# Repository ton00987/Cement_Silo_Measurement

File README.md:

# Cement_Silo_Measurement
/*
* Demo   : Silo measurement 
* VERSION: 0.1 (2/8/2019)
*
* MCU    : ESP32(ESP-WROOM-32)
*
* Output : Wifi
*        : BLYNK
*        : ThingSpeak
*
* Demo   : BLYNK -> "SILO MEASUREMENT"
*        : Blynk library V0.6.1
*        : BME280 
*        : MPU6050
*        :  
* Widget : RESET_B_pin              V1
*        : Widget_HEIGHT_BME        V5
*        : Widget_HEIGHT_MPU        V6
*        : Widget_Terminal          V7
*        : Widget_LED_RED_Status    V14
*        : Widget_LED_GREEN_Status  V27
*        : Widget_LED_BLUE_Status   V26
*/

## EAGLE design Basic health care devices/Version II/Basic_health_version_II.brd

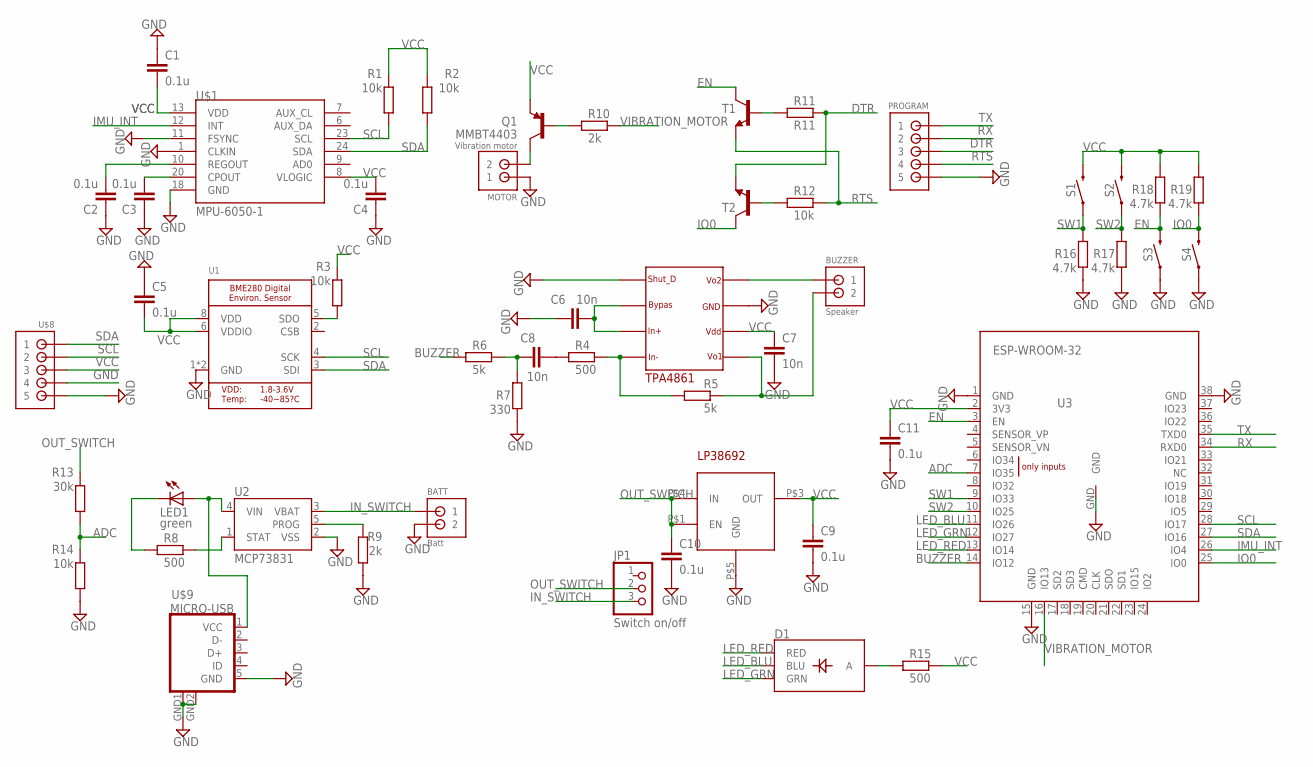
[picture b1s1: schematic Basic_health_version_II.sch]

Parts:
BATT: Batt; JST_B2B-PH_HEADER
BUZZER: Speaker; JST_B2B-PH_HEADER
C1, C2, C3, C4, C5, C9, C10, C11: 0.1u; C0603K
C6, C7, C8: 10n; C0603K
D1: LED-RGB-CASMD; LED-TRICOLOR-SMD
JP1: Switch on/off; 1X03
LED1: green; CHIPLED_0805
MOTOR: Vibration motor; JST_B2B-PH_HEADER
PROGRAM: Program port; JST_B5B-PH_HEADER
Q1: MMBT4403; SOT23-3
R1, R2, R3, R12, R14: 10k; R0603
R4, R8, R15: 500; R0603
R5, R6: 5k; R0603
R7: 330; R0603
R9, R10: 2k; R0603
R11: R11; R0603
R13: 30k; R0603
R16, R17, R18, R19: 4.7k; R0603
S1, S2, S3, S4: MOMENTARY-SWITCH-SPST-PTH-RIGHT-ANGLE; TACTILE_SWITCH_PTH_RIGHT_ANGLE
T1, T2: BC817-16-NPN-SOT23-BEC; SOT23-BEC
U1: BME280
U2: MCP73831; SOT23-5
U3: ESP-WROOM-32
U$1: MPU-6050-1; QFN-24-4MM2
U$2: TPA4861; SOIC8
U$5: LP38692_3.3V; SOT-223-4
U$8: JST-PH_5-PIN_HEADER; JST_B5B-PH_HEADER
U$9: MICRO-USB

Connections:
ADC: R13.1, R14.2, U3.7 (IO35)
BUZZER: R6.2, U3.14 (IO12)
DTR: PROGRAM.P3 (3), R11.1, T2.E
EN: R18.2, S3.2, T1.C, U3.3 (EN)
GND: BATT.P2 (2), C1.1, C2.1, C3.1, C4.1, C5.1, C6.2, C7.2, C9.2, C10.2, C11.2, MOTOR.P1 (1), PROGRAM.P5 (5), R7.2, R9.2, R14.1, R16.2, R17.2, S3.1, S4.1, U1.1 (GND), U1.7 (GND), U2.2 (VSS), U3.1 (GND), U3.15 (GND), U3.38 (GND), U3.GND, U$1.1 (CLKIN), U$1.11 (FSYNC), U$1.18 (GND), U$2.P$1, U$2.P$7, U$5.P$5 (GND), U$8.P4 (4), U$8.P5 (5), U$9.5 (GND), U$9.GND1 (GND), U$9.GND2 (GND)
IMU_INT: U3.26 (IO4), U$1.12 (INT)
IN_SWITCH: BATT.P1 (1), JP1.3, U2.3 (VBAT)
IO0: R19.2, S4.2, T2.C, U3.25 (IO0)
LED_BLU: D1.B (BLU), U3.11 (IO26)
LED_GRN: D1.G (GRN), U3.12 (IO27)
LED_RED: D1.R (RED), U3.13 (IO14)
unnamed: C6.1, U$2.P$2, U$2.P$3
unnamed: R3.1, U1.5 (SDO)
unnamed: C3.2, U$1.20 (CPOUT)
unnamed: C2.2, U$1.10 (REGOUT)
unnamed: R4.1, R5.2, U$2.P$4
unnamed: C8.2, R4.2
unnamed: BUZZER.P2 (2), R5.1, U$2.P$5
unnamed: BUZZER.P1 (1), U$2.P$8
unnamed: C8.1, R6.1, R7.1
unnamed: LED1.A, U2.4 (VIN), U$9.1 (VCC)
unnamed: LED1.C, R8.2
unnamed: R8.1, U2.1 (STAT)
unnamed: R9.1, U2.5 (PROG)
unnamed: Q1.1 (B), R10.2
unnamed: MOTOR.P2 (2), Q1.3 (C)
unnamed: R12.2, T2.B
unnamed: R11.2, T1.B
unnamed: D1.A, R15.2
OUT_SWITCH: C10.1, JP1.2, R13.2, U$5.P$1 (EN), U$5.P$4 (IN)
RTS: PROGRAM.P4 (4), R12.1, T1.E
RX: PROGRAM.P2 (2), U3.34 (RXD0)
SCL: R1.1, U1.4 (SCK), U3.28 (IO17), U$1.23 (SCL), U$8.P2 (2)
SDA: R2.1, U1.3 (SDI), U3.27 (IO16), U$1.24 (SDA), U$8.P1 (1)
SW1: R16.1, S1.1, U3.9 (IO33)
SW2: R17.1, S2.1, U3.10 (IO25)
TX: PROGRAM.P1 (1), U3.35 (TXD0)
VCC: C1.2, C4.2, C5.2, C7.1, C9.1, C11.1, Q1.2 (E), R1.2, R2.2, R3.2, R15.1, R18.1, R19.1, S1.2, S2.2, U1.6 (VDDIO), U1.8 (VDD), U3.2 (3V3), U$1.8 (VLOGIC), U$1.13 (VDD), U$2.P$6, U$5.P$3 (OUT), U$8.P3 (3)
VIBRATION_MOTOR: R10.1, U3.16 (IO13)

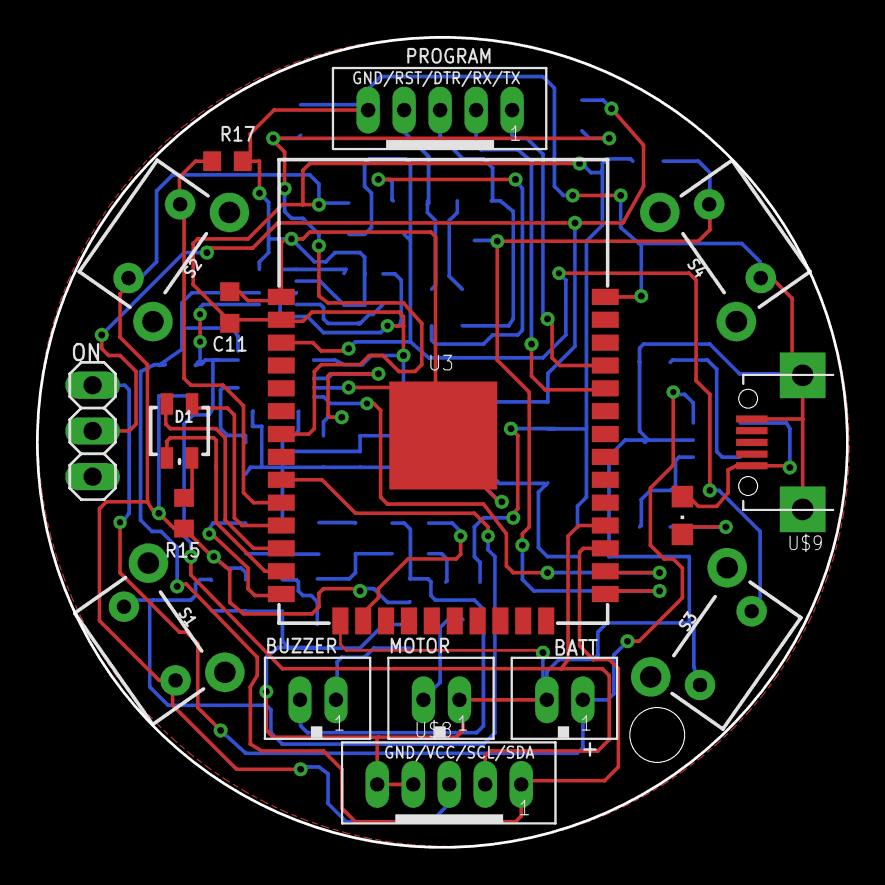
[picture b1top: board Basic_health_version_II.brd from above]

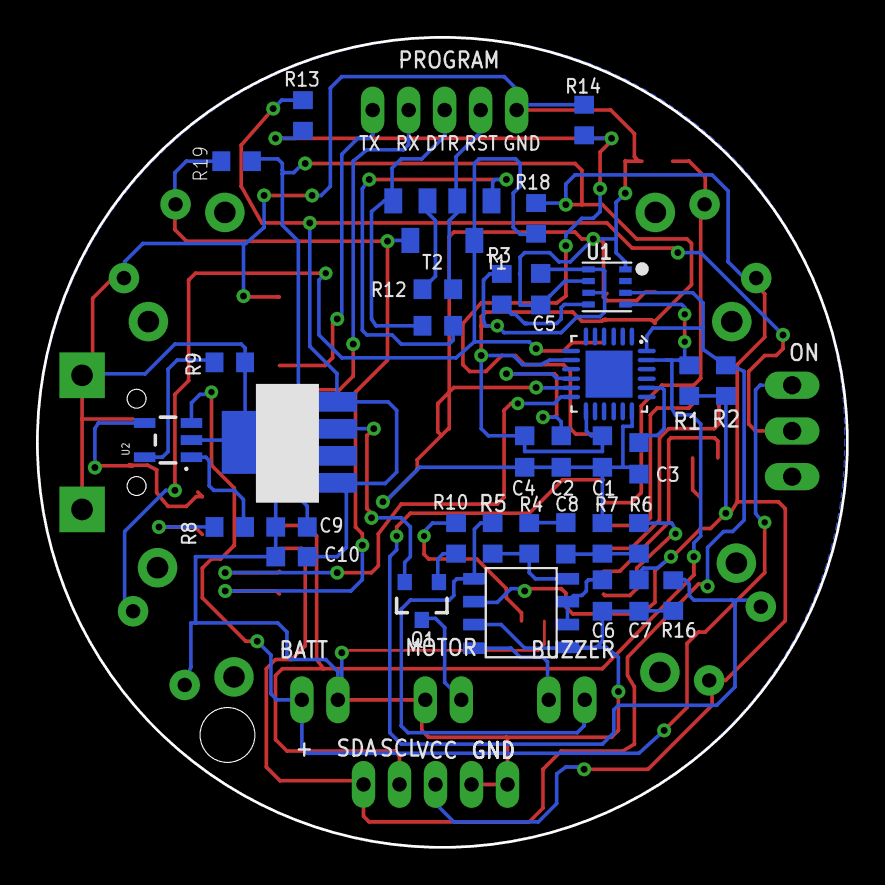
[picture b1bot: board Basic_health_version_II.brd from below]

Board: 2 copper layers, 45.0 x 45.0 mm, 52 parts (35 on the bottom side), 39 nets.

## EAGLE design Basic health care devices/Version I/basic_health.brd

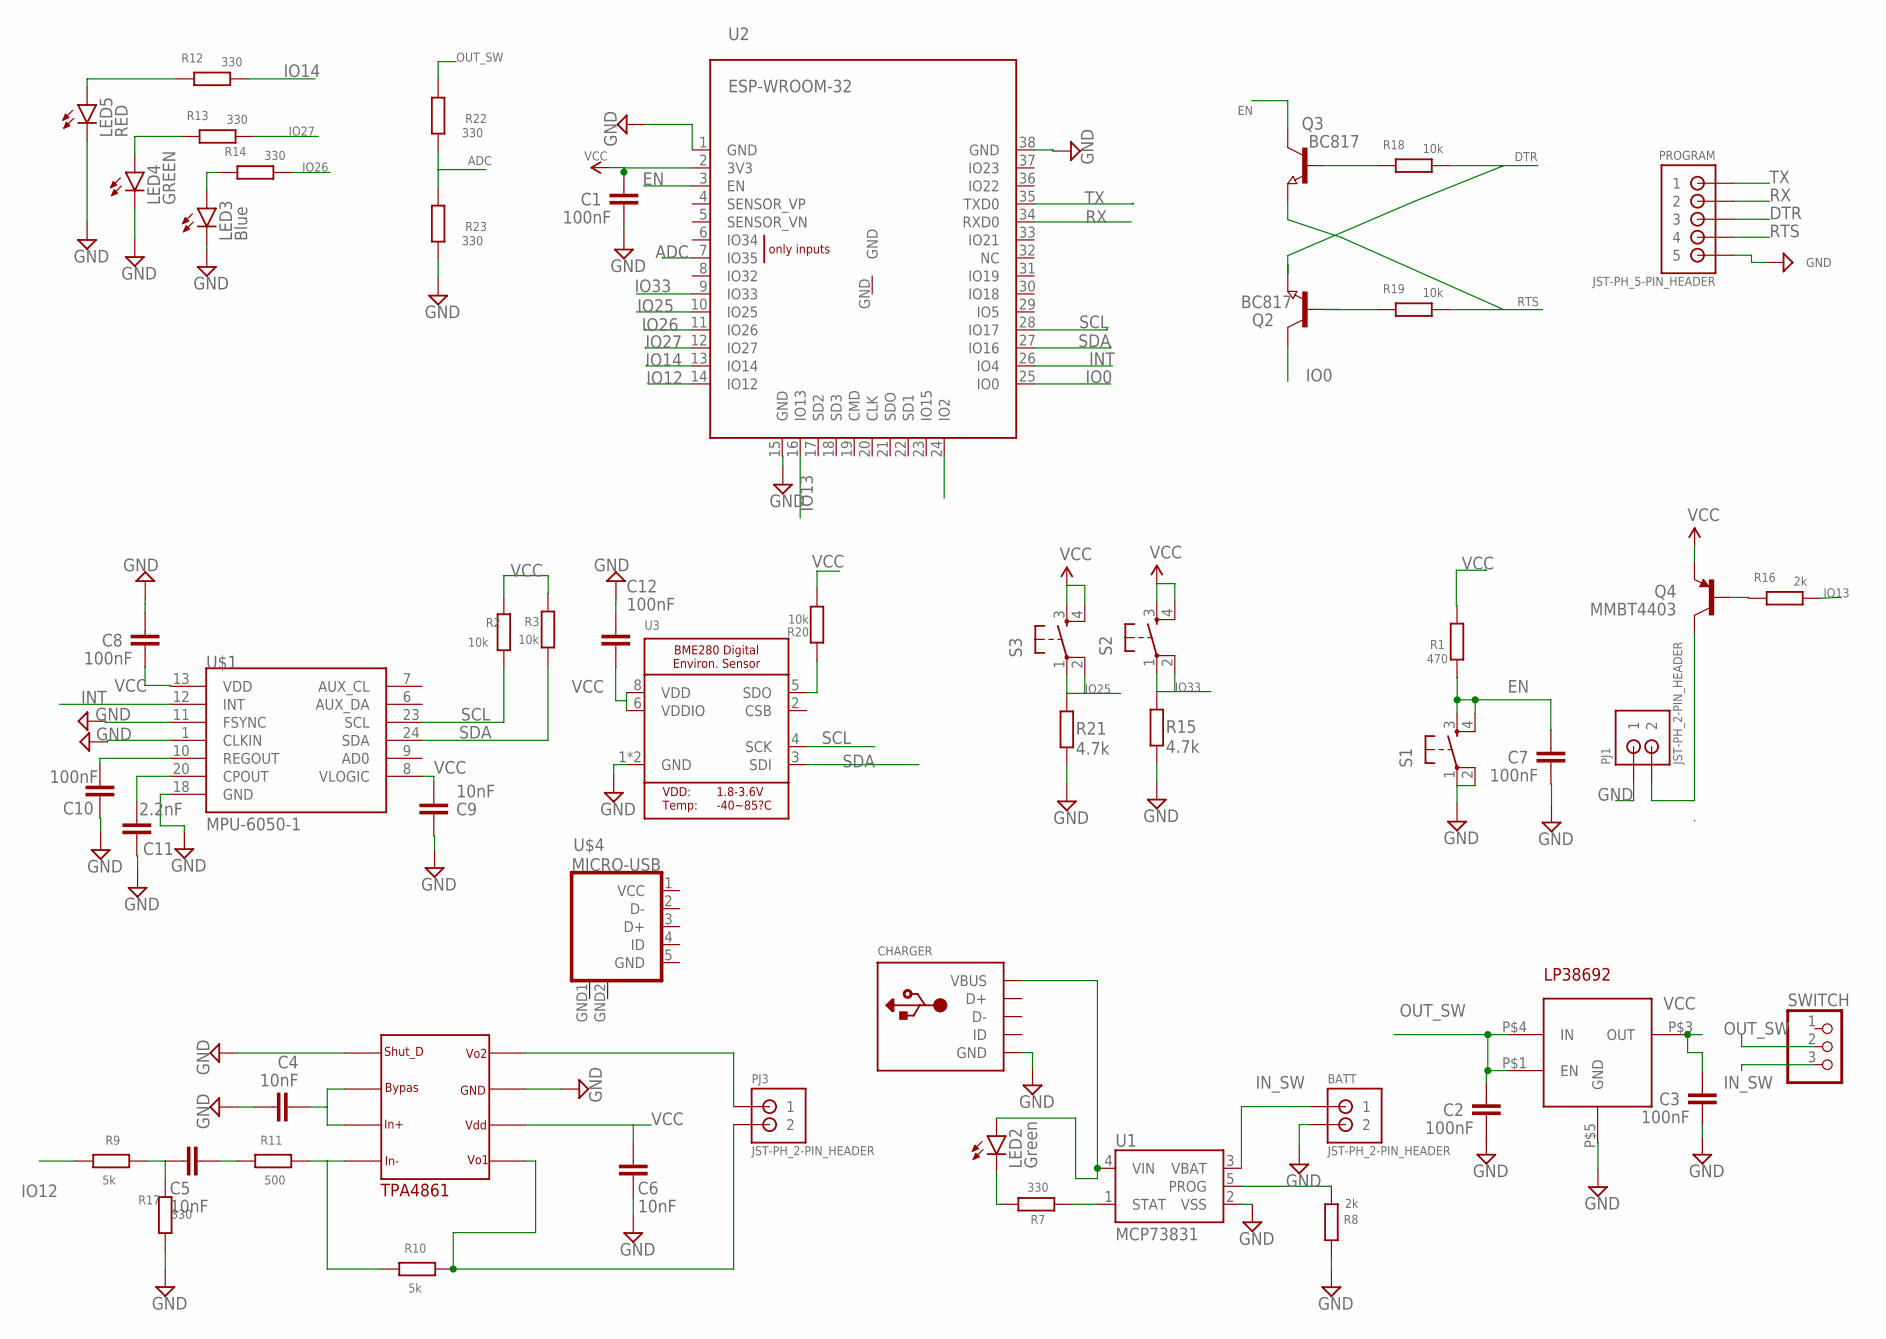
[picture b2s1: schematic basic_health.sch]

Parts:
BATT: JST-PH_2-PIN_HEADER; JST_B2B-PH_HEADER
C1, C2, C3, C7, C8, C10, C12: 100nF; 0603-CAP
C4, C5, C6, C9: 10nF; 0603-CAP
C11: 2.2nF; 0603-CAP
CHARGER: USBMINIB; USB-MINIB
LED2: Green; FKIT-LED-1206
LED3: Blue; FKIT-LED-1206
LED4: GREEN; FKIT-LED-1206
LED5: RED; FKIT-LED-1206
PJ1, PJ3: JST-PH_2-PIN_HEADER; JST_B2B-PH_HEADER
PROGRAM: JST-PH_5-PIN_HEADER; JST_B5B-PH_HEADER
Q2, Q3: BC817; SOT23
Q4: MMBT4403; SOT23-3
R1: 470; R0805
R2, R3, R18, R19, R20: 10k; R0805
R7, R12, R13, R14, R17, R22, R23: 330; R0805
R8, R16: 2k; R0805
R9, R10: 5k; R0805
R11: 500; R0805
R15, R21: 4.7k; R0805
S1, S2, S3: TAC_SWITCHPTH; TACTILE-PTH
SWITCH: PINHD-1X3/90; 1X03/90
U1: MCP73831; SOT23-5
U2: ESP-WROOM-32
U3: BME280
U$1: MPU-6050-1; QFN-24-4MM2
U$2: TPA4861; SOIC8
U$3: LP38692_3.3V; SOT-223-4
U$4: MICRO-USB

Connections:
ADC: R22.1, R23.2, U2.7 (IO35)
DTR: PROGRAM.P3 (3), Q2.2 (E), R18.2
EN: C7.1, Q3.3 (C), R1.2, S1.3, S1.4, U2.3 (EN)
GND: BATT.P2 (2), C1.2, C2.2, C3.2, C4.2, C6.2, C7.2, C8.1, C9.1, C10.1, C11.1, C12.1, CHARGER.GND, LED3.C, LED4.C, LED5.C, PJ1.P1 (1), PROGRAM.P5 (5), R8.1, R15.2, R17.1, R21.2, R23.1, S1.1, S1.2, U1.2 (VSS), U2.1 (GND), U2.15 (GND), U2.38 (GND), U3.1 (GND), U3.7 (GND), U$1.1 (CLKIN), U$1.11 (FSYNC), U$1.18 (GND), U$2.P$1, U$2.P$7, U$3.P$5 (GND), U$4.5 (GND), U$4.GND1 (GND), U$4.GND2 (GND)
INT: U2.26 (IO4), U$1.12 (INT)
IN_SW: BATT.P1 (1), SWITCH.3, U1.3 (VBAT)
IO0: Q2.3 (C), U2.25 (IO0)
IO12: R9.1, U2.14 (IO12)
IO13: R16.2, U2.16 (IO13)
IO14: R12.2, U2.13 (IO14)
IO25: R21.1, S3.1, S3.2, U2.10 (IO25)
IO26: R14.2, U2.11 (IO26)
IO27: R13.2, U2.12 (IO27)
IO33: R15.1, S2.1, S2.2, U2.9 (IO33)
unnamed: C10.2, U$1.10 (REGOUT)
unnamed: C11.2, U$1.20 (CPOUT)
unnamed: PJ1.P2 (2), Q4.3 (C)
unnamed: LED4.A, R13.1
unnamed: LED3.A, R14.1
unnamed: Q4.1 (B), R16.1
unnamed: CHARGER.VBUS, LED2.A, U1.4 (VIN)
unnamed: R10.1, R11.2, U$2.P$4
unnamed: R7.2, U1.1 (STAT)
unnamed: PJ3.P2 (2), R10.2, U$2.P$5
unnamed: Q3.1 (B), R18.1
unnamed: Q2.1 (B), R19.1
unnamed: LED2.C, R7.1
unnamed: R8.2, U1.5 (PROG)
unnamed: C4.1, U$2.P$2, U$2.P$3
unnamed: C5.1, R11.1
unnamed: PJ3.P1 (1), U$2.P$8
unnamed: C5.2, R9.2, R17.2
unnamed: LED5.A, R12.1
unnamed: R20.1, U3.5 (SDO)
OUT_SW: C2.1, R22.2, SWITCH.2, U$3.P$1 (EN), U$3.P$4 (IN)
RTS: PROGRAM.P4 (4), Q3.2 (E), R19.2
RX: PROGRAM.P2 (2), U2.34 (RXD0)
SCL: R2.1, U2.28 (IO17), U3.4 (SCK), U$1.23 (SCL)
SDA: R3.1, U2.27 (IO16), U3.3 (SDI), U$1.24 (SDA)
TX: PROGRAM.P1 (1), U2.35 (TXD0)
VCC: C1.1, C3.1, C6.1, C8.2, C9.2, C12.2, Q4.2 (E), R1.1, R2.2, R3.2, R20.2, S2.3, S2.4, S3.3, S3.4, U2.2 (3V3), U3.6 (VDDIO), U3.8 (VDD), U$1.8 (VLOGIC), U$1.13 (VDD), U$2.P$6, U$3.P$3 (OUT), U$4.1 (VCC)

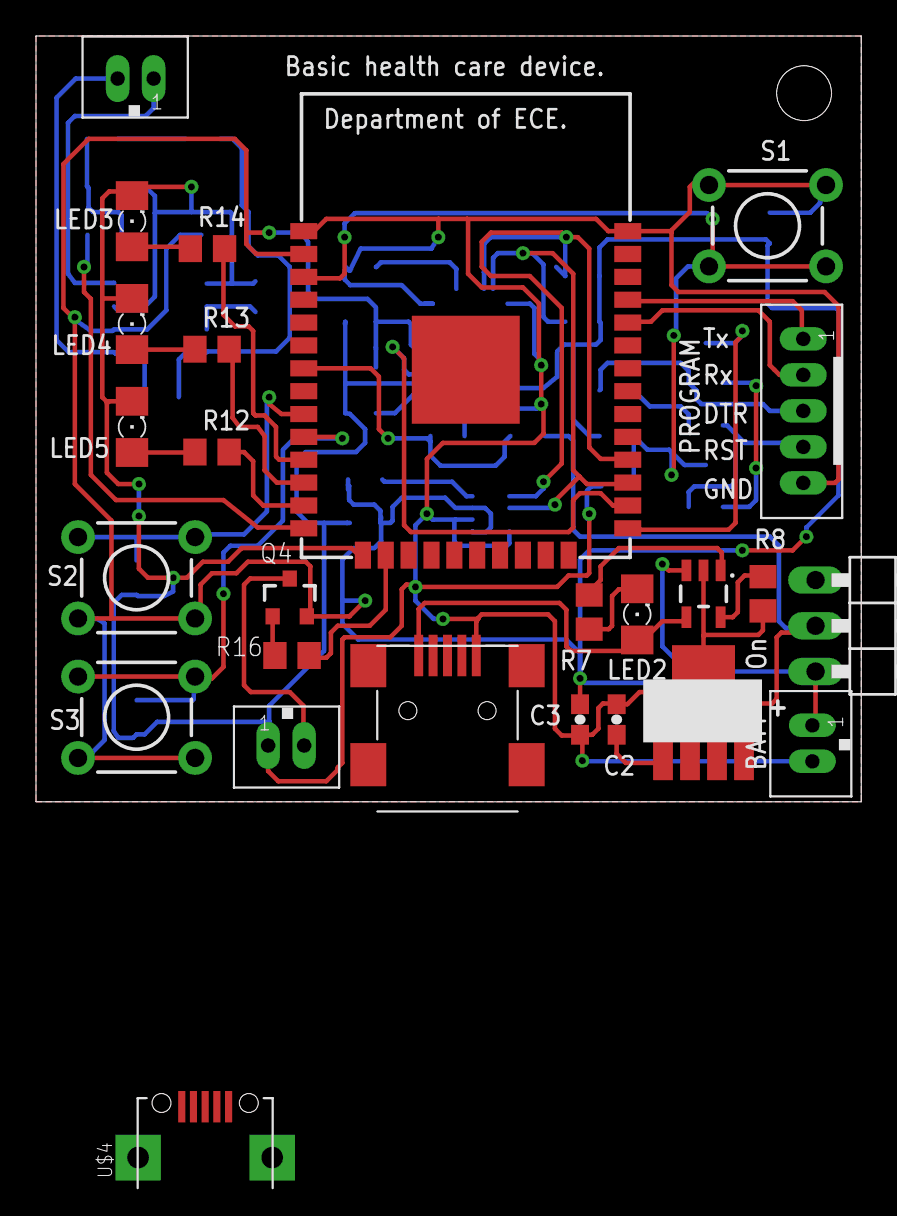
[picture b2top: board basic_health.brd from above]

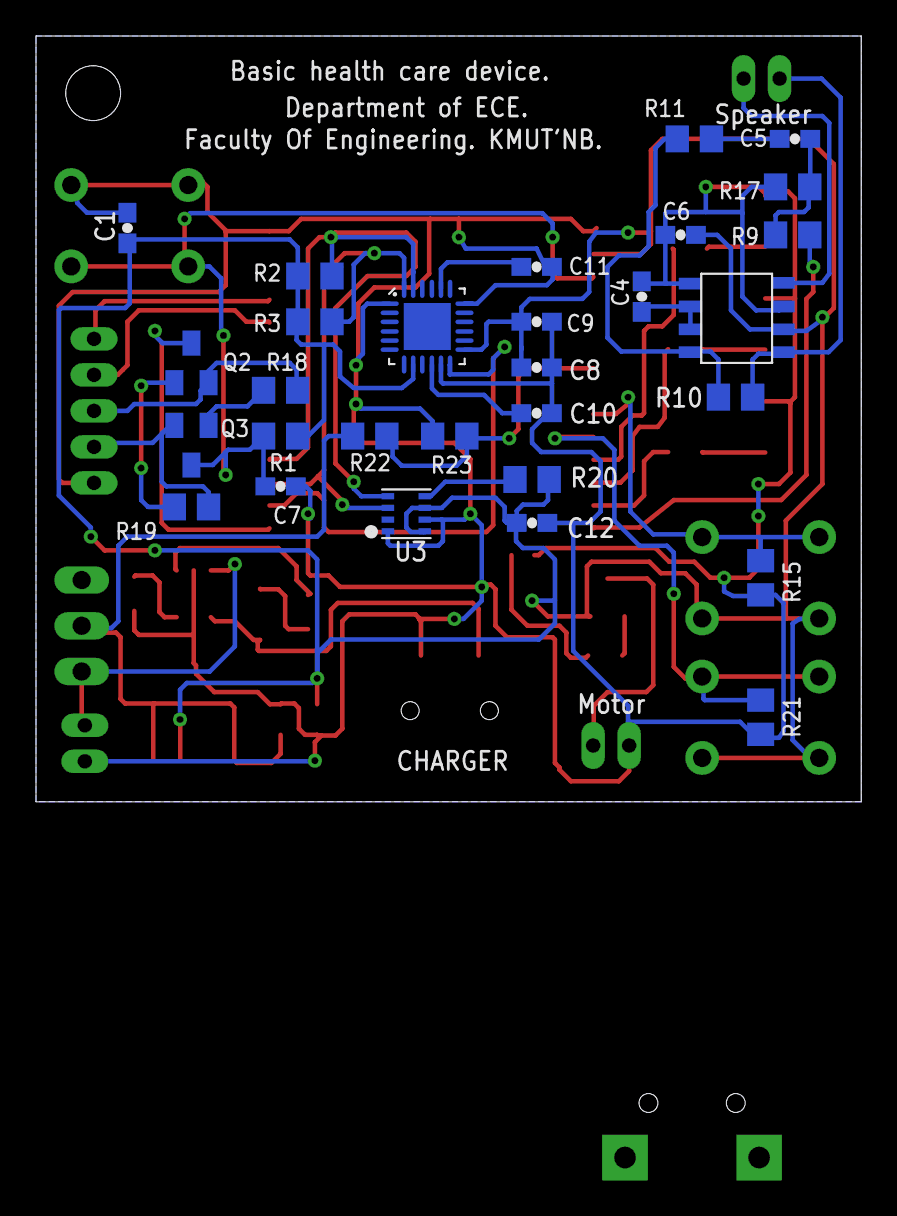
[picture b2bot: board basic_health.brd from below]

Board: 2 copper layers, 45.8 x 42.5 mm, 55 parts (29 on the bottom side), 41 nets.

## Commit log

2019-07-01 Add reference and Last work
2019-07-02 EEPROM clear and read libraries
2019-08-02 add BME MPU BLYNK THINGHSPEAK
2019-09-18 fixblynk
2019-11-06 Silo Measurement
2019-11-06 fix blynk connect ok
2019-11-06 v0.2.5 BLACK
2019-11-06 v0.3 mpu6050x2
2019-11-06 fix internet connection and change data in eeprom
2019-11-06 fix internet connection and change data in eeprom (mpu6050x2)
2019-11-06 v0.3.6

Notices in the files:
parts and their libraries:
SparkFun-Aesthetics: Licensing: Creative Commons ShareAlike 4.0 International - https://creativecommons.org/licenses/by-sa/4.0
